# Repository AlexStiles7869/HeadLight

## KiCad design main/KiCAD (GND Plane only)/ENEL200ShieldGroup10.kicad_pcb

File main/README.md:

# HeadLight

## Build Instructions

In Unix like terminal run the following:

gcc main.c Load_Cell.c LED_Group.c LED_Group_Collection.c voltage.c && ./a.out

## Environment Configuration

To modify max voltage and common mode, see voltage.c.

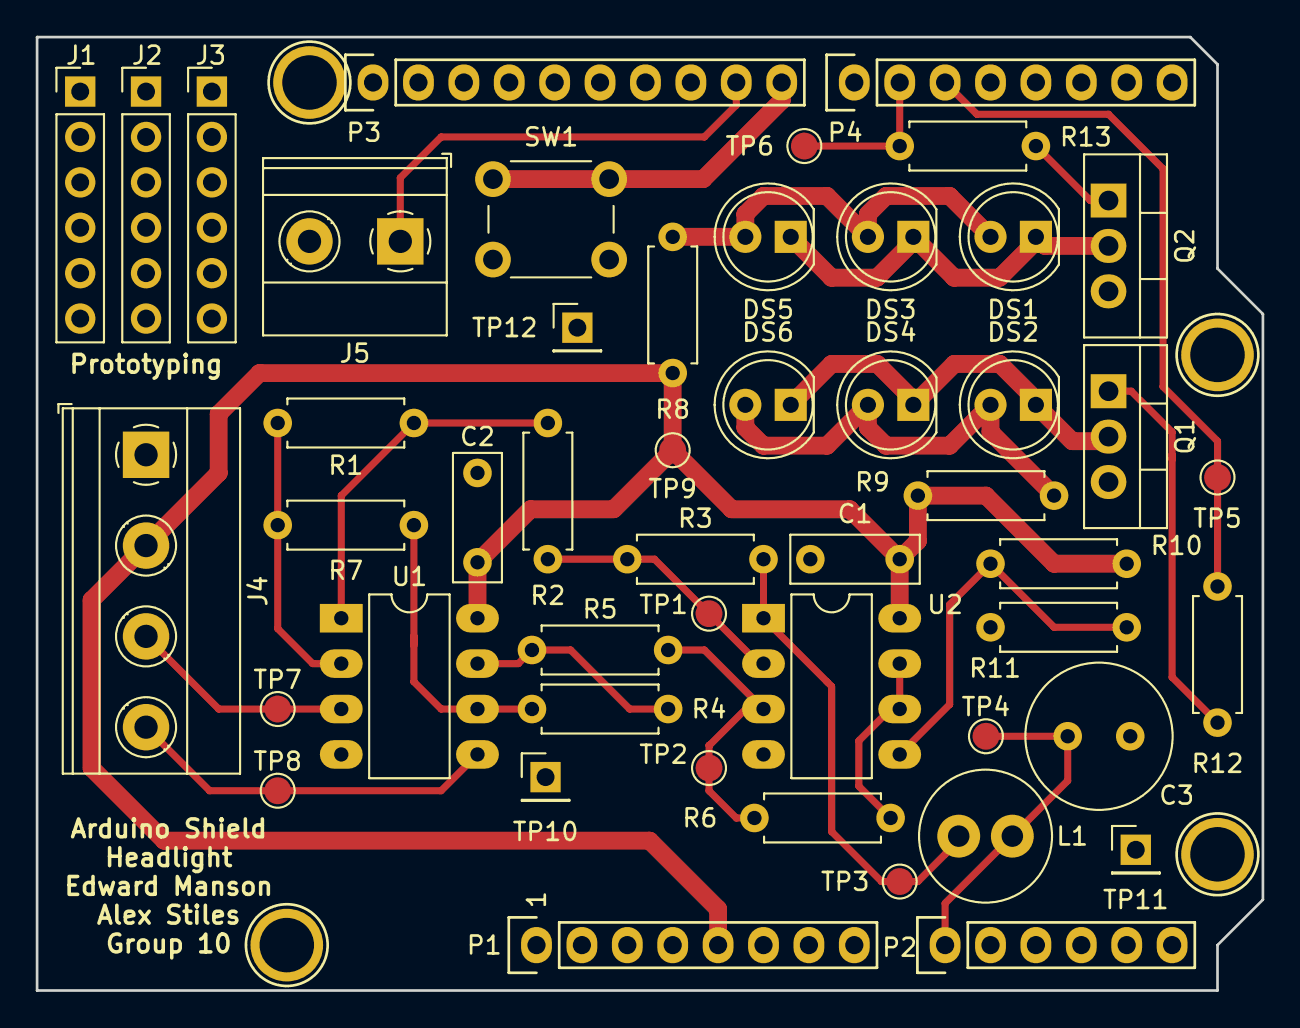
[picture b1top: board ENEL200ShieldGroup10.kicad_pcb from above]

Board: 2 copper layers, 68.6 x 53.3 mm, 53 parts (0 on the bottom side), 24 nets.

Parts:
C1, C2: 100n; C_Rect_L7.0mm_W2.5mm_P5.00mm
C3: 470u; C_Radial_D8.0mm_H11.5mm_P3.50mm
DS1, DS2, DS3, DS4, DS5, DS6: C512A; LED_D5.0mm
J1, J2, J3: M3; PinHeader_1x06_P2.54mm_Vertical
J4: Screw_Terminal_01x04; TerminalBlock_Phoenix_MKDS-1,5-4-5.08_1x04_P5.08mm_Horizont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
J5: Screw_Terminal_01x02; TerminalBlock_Phoenix_MKDS-1,5-2-5.08_1x02_P5.08mm_Horizont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
L1: 22u; L_Radial_D7.2mm_P3.00mm_MuRATA_1700
P1: Power; Socket_Strip_Arduino_1x08
P2: Analog; Socket_Strip_Arduino_1x06
P3: Digital; Socket_Strip_Arduino_1x10
P4: Digital; Socket_Strip_Arduino_1x08
P5, P6, P7, P8: CONN_01X01; Arduino_1pin
Q1, Q2: IRF740; TO-220-3_Vertical
R1, R2, R3, R4, R5, R6: 10k; R_Axial_DIN0207_L6.3mm_D2.5mm_P7.62mm_Horizontal
R7: 33R; R_Axial_DIN0207_L6.3mm_D2.5mm_P7.62mm_Horizontal
R8, R9: 22R; R_Axial_DIN0207_L6.3mm_D2.5mm_P7.62mm_Horizontal
R10, R11: 1M; R_Axial_DIN0207_L6.3mm_D2.5mm_P7.62mm_Horizontal
R12, R13: 100R; R_Axial_DIN0207_L6.3mm_D2.5mm_P7.62mm_Horizontal
SW1: SW_SPST; SW_PUSH_6mm
TP1, TP2, TP3, TP4, TP5, TP6, TP7, TP8, TP9: TestPoint; TestPoint_Pad_D1.5mm
TP10, TP11, TP12: TestPoint; PinHeader_1x01_P2.54mm_Vertical
U1, U2: UC_TLV272; DIP-8_W7.62mm_LongPads

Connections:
+2V5: R6.2, U2.6, U2.7
+5V: C1.1, C2.2, J4.2, P1.5, R8.1, R9.1, R10.1, TP9.1, U1.8, U2.8
+INPUT: J4.4, TP8.1, U1.5
-INPUT: J4.3, TP7.1, U1.3
AMP_OUT: C3.1, L1.2, P2.1, TP4.1
Button: P3.10, SW1.2
EXTRA_O: J5.1, P3.9
GND: C1.2, C2.1, C3.2, J4.1, J5.2, P1.6, P1.7, P3.4, Q1.3, Q2.3, R11.2, SW1.1, TP10.1, TP11.1, TP12.1, U1.4, U2.4
LED_1: P4.3, R12.1, TP5.1
LED_2: P4.2, R13.2, TP6.1
unnamed: DS1.1, DS3.1, DS5.1, Q2.2
unnamed: DS1.2, DS3.2, DS5.2, R8.2
unnamed: DS2.1, DS4.1, DS6.1, Q1.2
unnamed: DS2.2, DS4.2, DS6.2, R9.2
unnamed: L1.1, R3.1, TP3.1, U2.1
unnamed: Q1.1, R12.2
unnamed: Q2.1, R13.1
unnamed: R1.1, R2.2, U1.1
unnamed: R1.2, R7.1, U1.2
unnamed: R2.1, R3.2, TP1.1, U2.2
unnamed: R4.1, R7.2, U1.6
unnamed: R4.2, R5.1, U1.7
unnamed: R5.2, R6.1, TP2.1, U2.3
unnamed: R10.2, R11.1, U2.5

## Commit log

2021-08-11 First real commit
2021-08-11 Added mathematical formula for LED group brightness
2021-08-11 Added math formula for strain on load cell. Cleaned some stuff up.
2021-08-11 Added math for head angle, removed some printf() calls.
2021-08-13 Added main.ino for Arduino, kept main.c but added __cplusplus guard to ensure it doesn't cause problems. Cleaned up math formulas and added voltage.c / voltage.h to isolate environmental variables. U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
2021-08-14 Major changes and fixes. Cleaned up code and got working properly on Arduino. Fixed header guard for main.c (caused a lot of hassle). Designed in combo with tester circuit.
2021-08-14 Removed comment.
2021-08-14 removed comment, added executable to .gitignore
2021-08-15 Removed comment
2021-08-15 Added button to change between follow mode (default) and new full mode, which sets both LED groups to full brightness.
2021-08-27 Added the other stuff
2021-08-27 Moved it
2021-08-27 Added stuff in the design toolkit
2021-08-27 Added more building blocks
2021-08-27 Added more to the table
2021-08-27 Table stuff
2021-08-27 Added block diagram
2021-08-27 table
2021-08-27 tabularx -> longtable
2021-08-27 Added more testing stuff
2021-08-27 More table stuff
2021-08-27 centering error fixed
2021-08-27 Updated block diagram to include button
2021-08-27 Added Micro stuff
2021-08-27 Fixed C++ typesetting
2021-08-27 Added intro
2021-08-27 remove aux files
2021-08-27 remvd large code snippet in favor of ref to lsting
2021-08-27 Fixed urldate to not be American
2021-08-27 Listing numbering
2021-08-27 Final
